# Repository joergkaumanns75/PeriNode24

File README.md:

# PeriCharger – Ladegerät für 6 × 12 V / 2,4 Ah Blei-Gel (Perinode24)

Sechs unabhängige Ladekanäle (IUoU: Konstantstrom 0,6 A → 14,4 V → Erhaltung 13,65 V, temperaturkompensiert),
gesteuert von einem ESP32-S3 mit Weboberfläche. Versorgung: 24 V DC oder 230/240 V AC über ein Netzteil (Mean Well LRS-100-24).

| Ordner | Inhalt |
|---|---|
| [`kicad/`](kicad/) | KiCad-Projekt (`perinode24.kicad_pro`): Schaltplan (7 Blätter), 4-lagige Leiterplatte, JLCPCB-Stückliste mit LCSC-Nummern, Generator-Werkzeuge – siehe [kicad/README.md](kicad/README.md) |
| [`firmware/`](firmware/) | PlatformIO-Projekt für den ESP32-S3 (Arduino-Core 3.x): Ladesteuerung, WLAN, Weboberfläche, Host-Simulation – siehe [firmware/README.md](firmware/README.md) |

**Stand Leiterplatte:** geroutet und DRC-sauber. Noch sind 6 kurze Signalverbindungen an den Spannungsreglern von Hand zu ziehen (Liste in kicad/README.md).
Die Firmware ist auf dem PC simuliert und getestet, aber noch nicht auf echter Hardware.

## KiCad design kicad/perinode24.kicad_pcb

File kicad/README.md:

# Perinode24 – KiCad-Projekt Ladegerät 6 × 12 V / 2,4 Ah

Öffnen: `perinode24.kicad_pro` (KiCad 7; KiCad 8/9 konvertiert beim Speichern).

| Datei | Inhalt |
|---|---|
| `perinode24.kicad_sch` | Hauptblatt (A2): 24-V-DC-Eingang und Netzteil-Eingang mit Ideal-Dioden-ODER (LM74700), 5 V (LMR16006), 3,3 V (TLV75733), ESP32-S3-WROOM-1-N8R8, USB-C, I²C/1-Wire/OLED |
| `kanal1…6.kicad_sch` | je ein Ladekanal (A3): TPS54160A, CC/CV-Sollwertsteuerung, INA226 + INA181, Verpolschutz, PTC, Akku- und Sensoranschluss |
| `perinode24.kicad_sym` | Projektsymbole: TPS54160A (MSOP-10 PowerPAD), N-MOSFET SO-8 |
| `bom_jlcpcb.csv` | Stückliste im JLCPCB-Format (Comment, Designator, Footprint, LCSC Part #) |
| `perinode24_schaltplan.pdf` | PDF-Export aller Blätter |
| `tools/gen_schematic.py` | Generator – Werte/LCSC-Nummern in der Tabelle `P` ändern und neu erzeugen |

Jedes Bauteil hat die Felder **LCSC** und **MPN**. Diese Felder werden von JLCPCB-Exporttools übernommen, zum Beispiel vom Plugin „Fabrication Toolkit“ oder von „kicad-jlcpcb-tools“.

## Vor der Bestellung prüfen

- **C106/C206/… 47 pF (C1671):** Diese LCSC-Nummer ist nicht verifiziert. Alle anderen Nummern wurden im LCSC/JLCPCB-Katalog nachgeschlagen. Lagerbestand und die Einstufung Basic/Extended ändern sich laufend.
- **Alles SMD:** Stecker sind JST PH SMD.
  - J1/J2 (24 V): S6B-PH-SM4-TB, je 3 Pins parallel für + und −, 2 A pro Pin.
  - Akku + DS18B20: S4B-PH-SM4-TB mit Belegung 1 = Akku +, 2 = Akku − / GND, 3 = DQ, 4 = 3,3 V.
  - Display: Qwiic-Buchse SM04B-SRSS-TB.
  - Nur die Gehäuselaschen der USB-C-Buchse gehen durchs Board.
- **Footprint Drossel:** Die FXL1360-680-M (13,45 × 12,6 mm) liegt auf dem KiCad-Footprint L_TaiTech_TMPC1265_13.5x12.5mm. Pads gegen das Datenblatt des Herstellers prüfen.
- **TPS54160A:** Geprüft gegen das TI-Datenblatt SLVSB56C (Rev. C, Feb. 2014). Pinbelegung, VREF 0,8 V, EN-Schwelle 1,11–1,36 V (EN max. 5 V), BOOT 0,1 µF und Softstart (10 nF → 4 ms) stimmen. RT = 206033/f^1,0888, mit 390 k ergeben sich 316 kHz. Kompensation nach Abschnitt 9.2.2.10 (gmEA 97 µA/V, gmPS 6 A/V): Bei 0,6 A und einer wirksamen Ausgangskapazität von ca. 8 µF ergeben sich Rc ≈ 13,7 k und Cc ≈ 14 nF. Die gewählten 18 k / 15 nF ergeben eine Durchtrittsfrequenz fc ≈ 10 kHz, zulässig sind 4,1…15,9 kHz. Trotzdem mit Lastsprung messen.
- **Drossel:** FXL1360-680-M (C526032), 68 µH, 3 A Nennstrom, 4,5 A laut JLCPCB-Listing. Damit hat sie genug Reserve über der TPS54160A-Strombegrenzung (typ. 2,7 A). Ob die 4,5 A der Sättigungsstrom sind, in der I(L)-Kurve des Datenblatts prüfen.
- **ERC:** In KiCad ausführen. Die Prüfung hier erfolgte über den Netzlisten-Export: keine offenen Netze außer den bewusst nicht beschalteten Pins.
- Die Verbindungen sind über **Netzlabels** an Pin-Stichleitungen realisiert. Elektrisch ist das vollständig. Für eine schönere Darstellung kann man die Bauteile in KiCad umsortieren.

## Leiterplatte (`perinode24.kicad_pcb`)

**Stand: geroutet. DRC ohne Abstands-, Rand-, Bohr- oder Breitenverletzungen. 6 kurze Signalverbindungen sind noch von Hand zu ziehen** (siehe unten).

- **Format:** 200 × 131 mm, 4 Lagen, 1,6 mm (JLCPCB JLC04161H-7628), alle Bauteile SMD und oben.
- **Lagenaufbau:**
  - F.Cu: Bauteile, Signale, GND-Fläche
  - In1: durchgehende GND-Fläche (keine Leiterbahnen)
  - In2: Signale und +24-V-Fläche
  - B.Cu: Signale, GND-Fläche
- **Stitching:** rund 610 Vias im 5-mm-Raster verbinden die GND-Flächen. Unter der ESP32-Antenne ist auf allen Lagen kein Kupfer.
- **Netzklassen:**
  - Power24 0,8 mm: +24 V, Eingänge
  - Power 0,5 mm: Schaltknoten, Ausgang, Akku
  - Sense 0,3 mm: Shunt
  - Supply 0,3 mm: GND, +5 V, +3,3 V
  - Default 0,25 mm
  - Abstand 0,2 mm, Randabstand 0,2 mm (JLCPCB: ≥ 0,2 mm bei gefrästen Kanten), Mindestbahnbreite 0,12 mm
- `docs/platine_F.png`, `platine_In2.png`, `platine_B.png`: Ansichten der Lagen. `docs/drc_bericht.txt`: DRC-Bericht.

### Noch von Hand zu verbinden (in KiCad mit „Leiterbahn verlegen“, X)
| Kanal | Netz | von | nach |
|---|---|---|---|
| 1 | SS | U101 Pin 4 | C104 Pin 1 |
| 4 | SS | U401 Pin 4 | C404 Pin 1 |
| 6 | SS | U601 Pin 4 | C604 Pin 1 |
| 2 | EN_N | U201 Pin 3 | vorhandene Bahn auf In2 |
| 3 | EN_N | U301 Pin 3 | vorhandene Bahn auf In2 |
| 5 | EN_N | U501 Pin 3 → R504 Pin 1 → vorhandene Bahn (1,8 mm) |

Die Pins 3/4 des TPS54160A liegen im 0,5-mm-Raster zwischen bereits verlegten Bahnen. Am einfachsten verschiebt man die Bahn an Pin 5 (RT) etwas oder führt die Verbindung mit einem Via über B.Cu, wo unter dem IC Platz ist. Zwei winzige GND-Flächeninseln auf F.Cu werden nach dem Nachrouten mit einem Via angebunden oder können gelöscht werden. Danach Zonen füllen (B) und die DRC erneut ausführen.

### Wie die Leiterplatte entstanden ist (Werkzeuge in `tools/`)
1. `gen_pcb.py`: Footprints aus der Netzliste, Platzierung (Ankerplätze und automatische Platzierung), Umriss, Bohrungen, Flächen
2. `preroute.py`: kritische Anschlüsse der fein gerasterten ICs vorverlegen (TPS VIN → +24-V-Via, GND-Pins → Via bzw. Thermal-Pad) und fixieren
3. Export DSN, `dsn_classes.py` (Netzklassen ergänzen, GND für Freerouting ausblenden), **Freerouting 2.5.0** mit 10 Durchgängen
4. `import_ses.py`: Session einspielen
5. `postroute.py`: +24-V-Fläche auf In2, offene Pads an Flächen, Lücken schließen, Inseln, Stitching-Vias (alles mit KiCads Kollisionsprüfung)
6. `maze.py`: A*-Router für einzelne Restverbindungen
7. `check_pcb.py`: Zonen füllen und DRC. `set_netclasses.py` nach jedem Speichern über die API ausführen, weil KiCad 7 headless die Projekt-Netzklassen zurücksetzt.

Nach dem Nachrouten in KiCad: Gerber, Bohrdaten, BOM und CPL für JLCPCB erzeugen, zum Beispiel mit dem Plugin „Fabrication Toolkit“, das das Feld LCSC übernimmt.

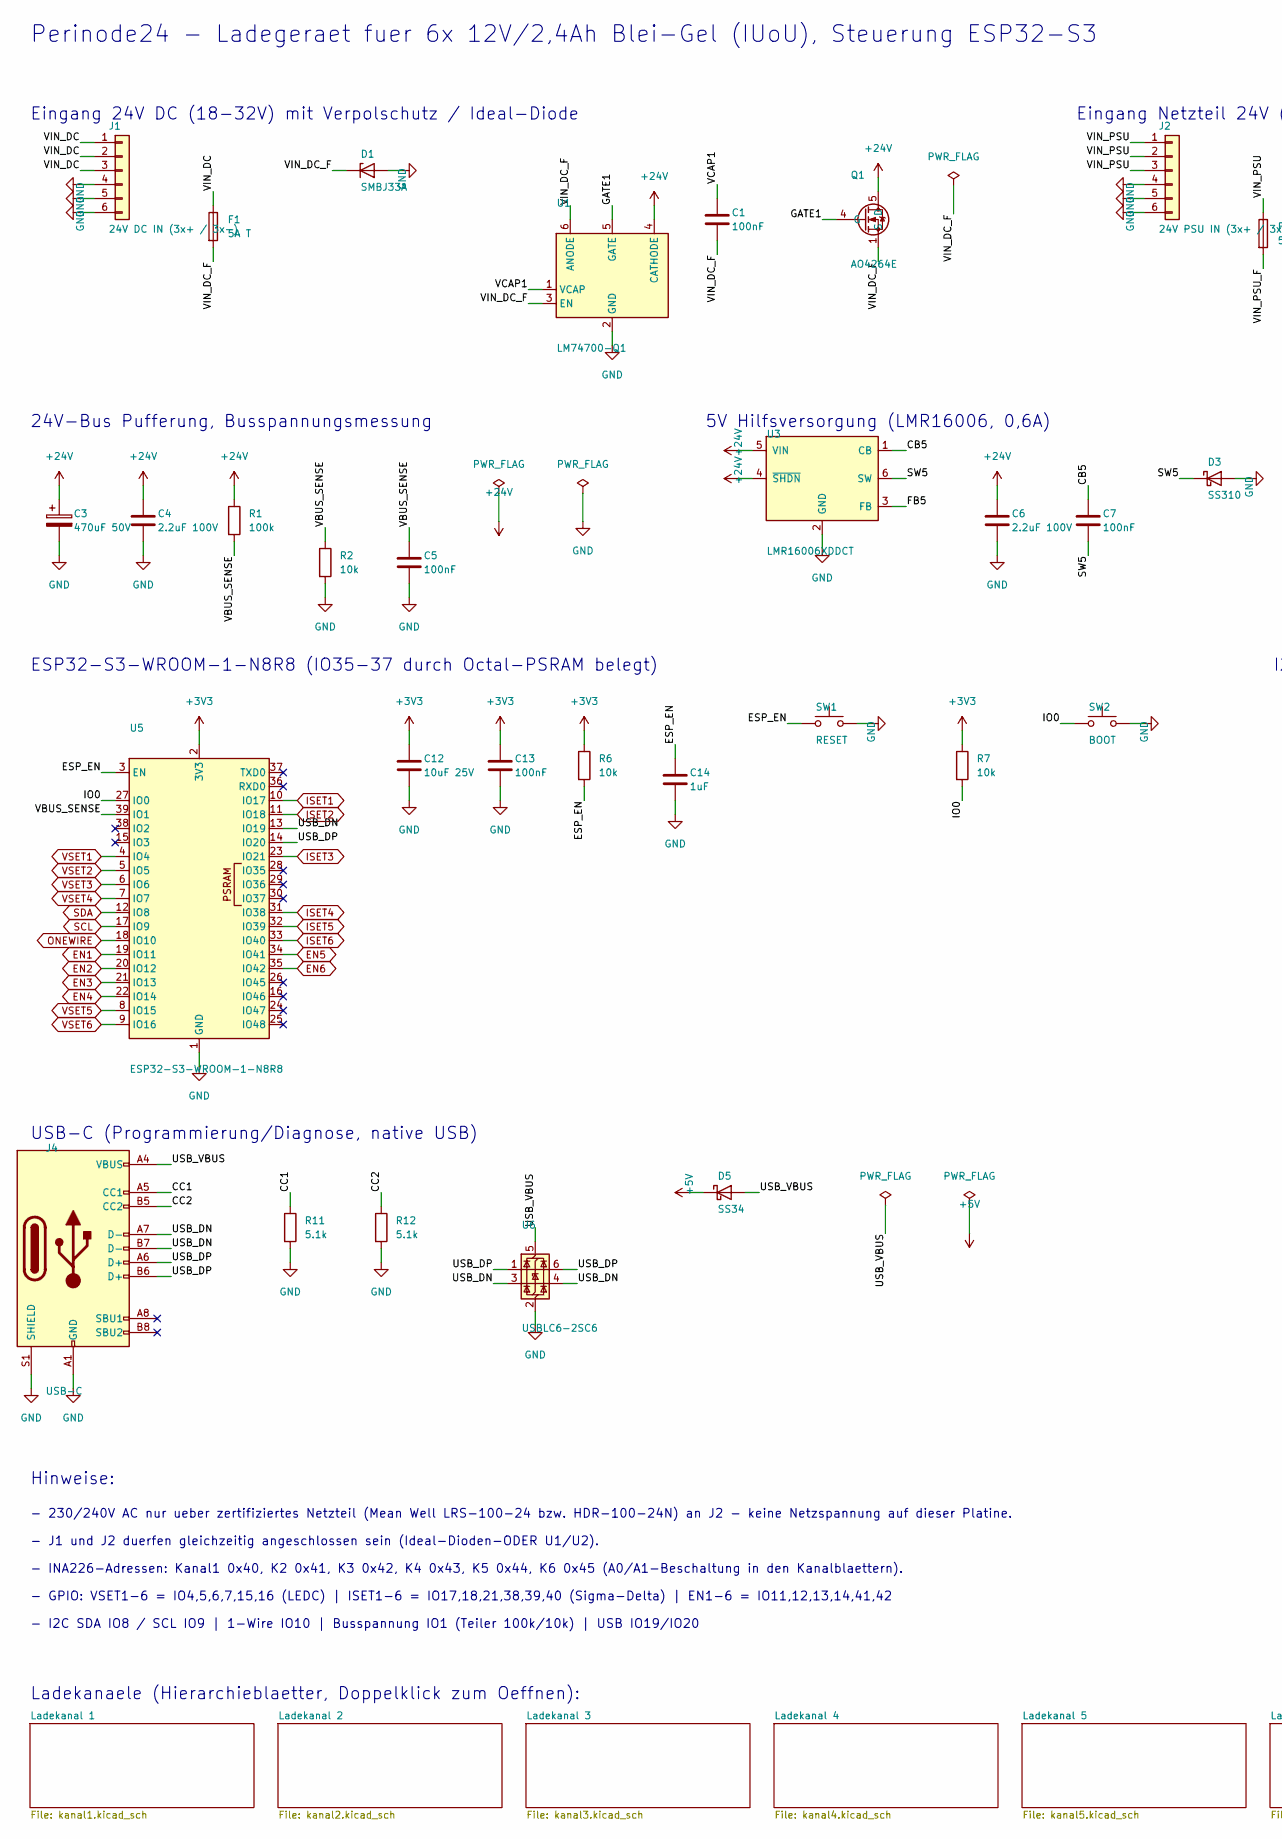
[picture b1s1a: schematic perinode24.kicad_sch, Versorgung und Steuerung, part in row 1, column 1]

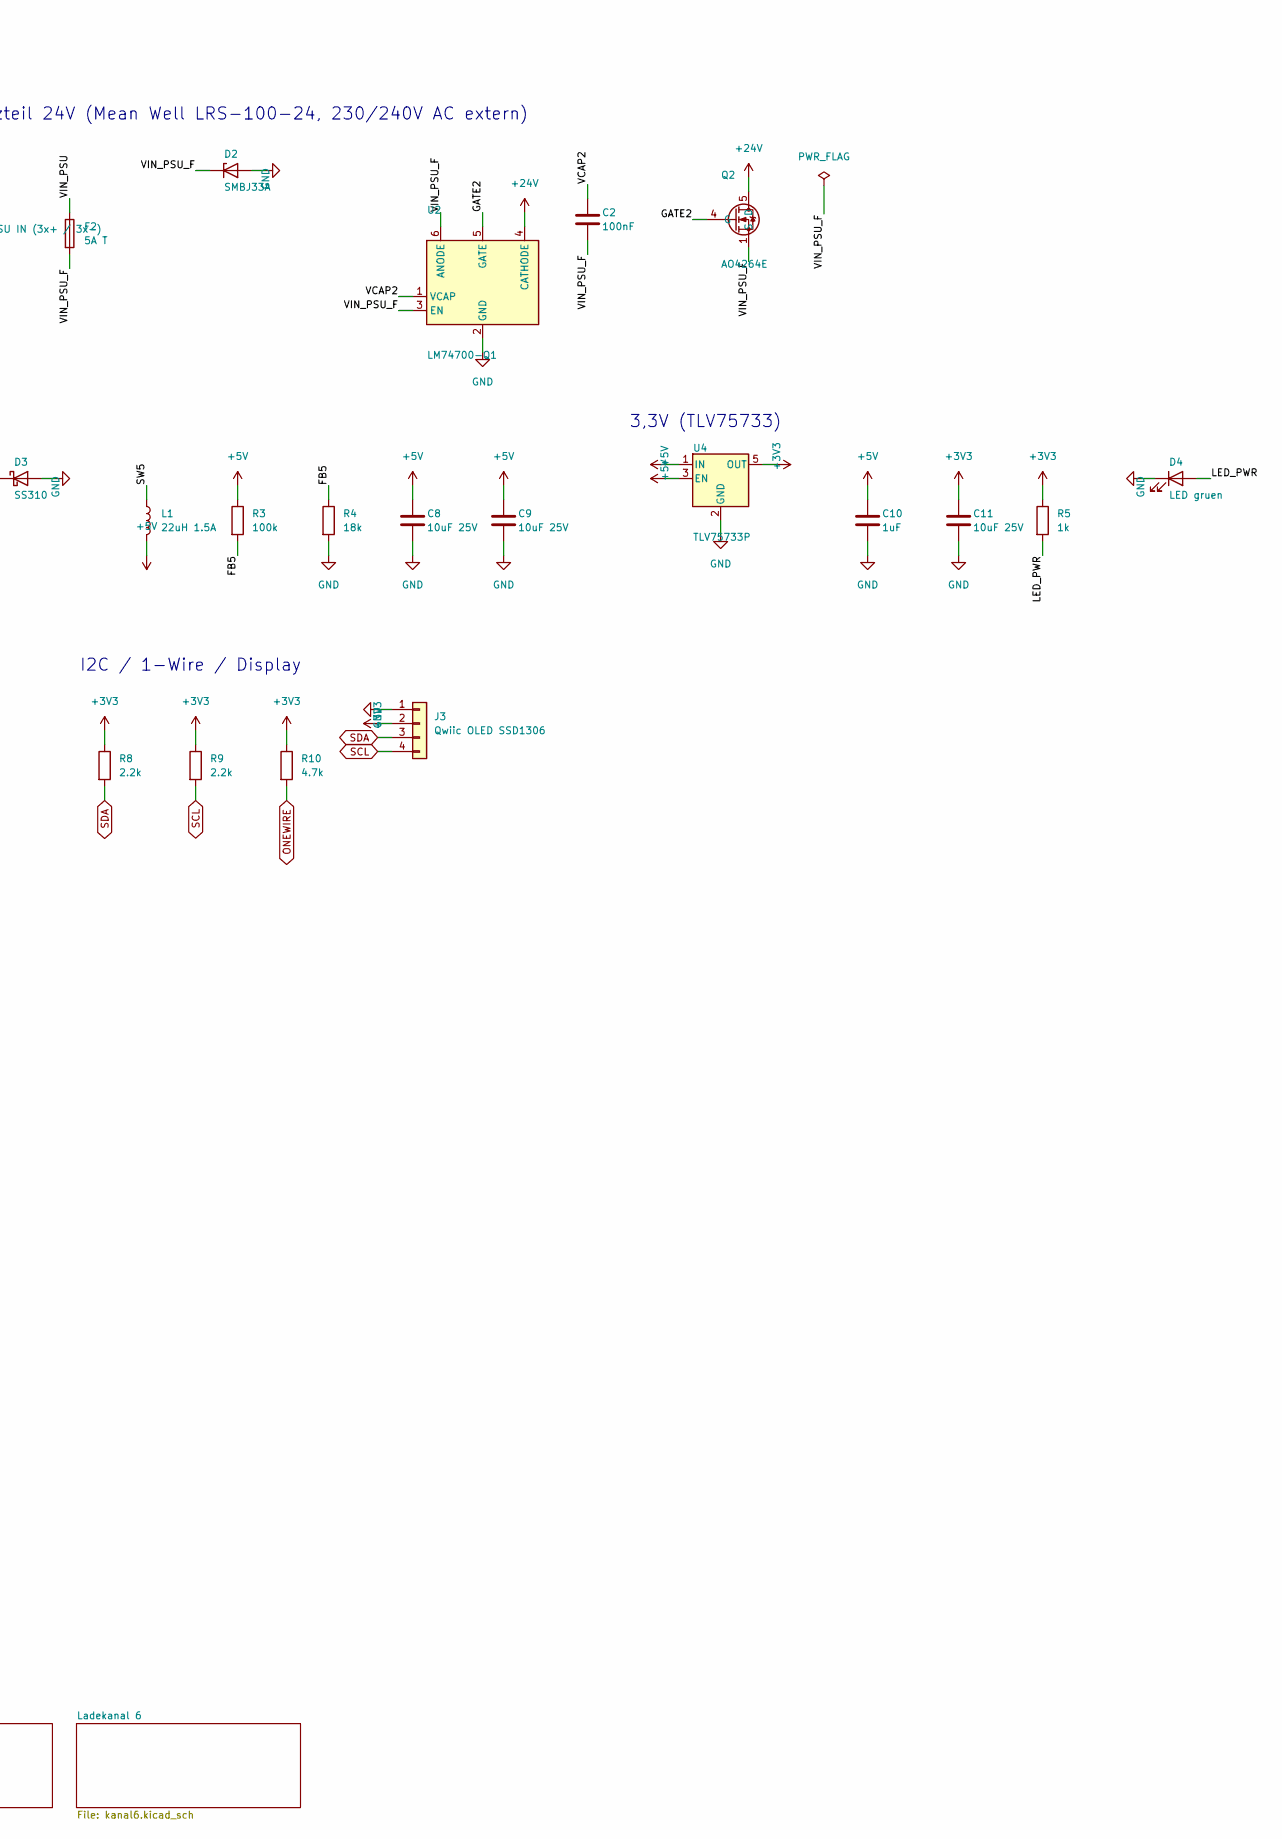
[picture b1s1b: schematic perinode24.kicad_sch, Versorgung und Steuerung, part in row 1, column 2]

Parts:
C1, C2, C5, C7, C13: 100nF; C_0603_1608Metric; MPN CC0603KRX7R9BB104; LCSC C14663
C3: 470uF 50V; CP_Elec_10x12.5; MPN EFVM050ADA471M10C0; LCSC C22469994
C4, C6: 2.2uF 100V; C_1210_3225Metric; MPN CL32B225KCJSNNE; LCSC C55151
C8, C9, C11, C12: 10uF 25V; C_0805_2012Metric; MPN CL21A106KAYNNNE; LCSC C15850
C10, C14: 1uF; C_0603_1608Metric; MPN CL10A105KB8NNNC; LCSC C15849
D1, D2: SMBJ33A; D_SMB; MPN SMBJ33A; LCSC C353366
D3: SS310; D_SMA; MPN SS310; LCSC C15874
D4: LED gruen; LED_0603_1608Metric; MPN 19-217/GHC-YR1S2/3T; LCSC C72043
D5: SS34; D_SMA; MPN SS34; LCSC C8678
F1, F2: 5A T; Fuse_Littelfuse-NANO2-451_453; MPN 0452005.MRL; LCSC C66503
J1: 24V DC IN (3x+ / 3x-); JST_PH_S6B-PH-SM4-TB_1x06-1MP_P2.00mm_Horizontal; MPN S6B-PH-SM4-TB(LF)(SN); LCSC C265405
J2: 24V PSU IN (3x+ / 3x-); JST_PH_S6B-PH-SM4-TB_1x06-1MP_P2.00mm_Horizontal; MPN S6B-PH-SM4-TB(LF)(SN); LCSC C265405
J3: Qwiic OLED SSD1306; JST_SH_SM04B-SRSS-TB_1x04-1MP_P1.00mm_Horizontal; MPN SM04B-SRSS-TB(LF)(SN); LCSC C160404
J4: USB-C; USB_C_Receptacle_HRO_TYPE-C-31-M-12; MPN TYPE-C-31-M-12; LCSC C165948
L1: 22uH 1.5A; L_Bourns_SRN6045TA; MPN SRN6045-220M; LCSC C780213
Q1, Q2: AO4264E; SOIC-8_3.9x4.9mm_P1.27mm; MPN AO4264E; LCSC C334232
R1, R3: 100k; R_0603_1608Metric; MPN 0603WAF1003T5E; LCSC C25803
R2, R6, R7: 10k; R_0603_1608Metric; MPN 0603WAF1002T5E; LCSC C25804
R4: 18k; R_0603_1608Metric; MPN 0603WAF1802T5E; LCSC C25810
R5: 1k; R_0603_1608Metric; MPN 0603WAF1001T5E; LCSC C21190
R8, R9: 2.2k; R_0603_1608Metric; MPN 0603WAF2201T5E; LCSC C4190
R10: 4.7k; R_0603_1608Metric; MPN 0603WAF4701T5E; LCSC C23162
R11, R12: 5.1k; R_0603_1608Metric; MPN 0603WAF5101T5E; LCSC C23186
SW1: RESET; SW_Push_1P1T_XKB_TS-1187A; MPN TS-1187A-B-A-B; LCSC C318884
SW2: BOOT; SW_Push_1P1T_XKB_TS-1187A; MPN TS-1187A-B-A-B; LCSC C318884
U1, U2: LM74700-Q1; SOT-23-6; MPN LM74700QDBVRQ1; LCSC C2941042
U3: LMR16006XDDCT; TSOT-23-6; MPN LMR16006XDDCT; LCSC C2070731
U4: TLV75733P; SOT-23-5; MPN TLV75733PDBVR; LCSC C485517
U5: ESP32-S3-WROOM-1-N8R8; ESP32-S3-WROOM-1; MPN ESP32-S3-WROOM-1-N8R8; LCSC C2913201
U6: USBLC6-2SC6; SOT-23-6; MPN USBLC6-2SC6; LCSC C7519

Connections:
+3V3: C11.1, C12.1, C13.1, J3.2, R5.1, R6.1, R7.1, R8.1, R9.1, R10.1, U4.5 (OUT), U5.2 (3V3); also elsewhere on the board
+5V: C8.1, C9.1, C10.1, D5.1 (K), L1.2, R3.1, U4.1 (IN), U4.3 (EN); also elsewhere on the board
+24V: C3.1, C4.1, C6.1, Q1.5 (D), Q1.6 (D), Q1.7 (D), Q1.8 (D), Q2.5 (D), Q2.6 (D), Q2.7 (D), Q2.8 (D), R1.1, U1.4 (CATHODE), U2.4 (CATHODE), U3.4 (~SHDN), U3.5 (VIN); also elsewhere on the board
/CB5: C7.1, U3.1 (CB)
/CC1: J4.A5 (CC1), R11.1
/CC2: J4.B5 (CC2), R12.1
/ESP_EN: C14.1, R6.2, SW1.1, U5.3 (EN)
/FB5: R3.2, R4.1, U3.3 (FB)
/GATE1: Q1.4 (G), U1.5 (GATE)
/GATE2: Q2.4 (G), U2.5 (GATE)
/IO0: R7.2, SW2.1, U5.27 (IO0)
/LED_PWR: D4.2 (A), R5.2
/SW5: C7.2, D3.1 (K), L1.1, U3.6 (SW)
/USB_DN: J4.A7 (D-), J4.B7 (D-), U5.13 (IO19), U6.3 (I/O2), U6.4 (I/O2)
/USB_DP: J4.A6 (D+), J4.B6 (D+), U5.14 (IO20), U6.1 (I/O1), U6.6 (I/O1)
/USB_VBUS: D5.2 (A), J4.A4 (VBUS), J4.A9 (VBUS), J4.B4 (VBUS), J4.B9 (VBUS), U6.5 (VBUS)
/VBUS_SENSE: C5.1, R1.2, R2.1, U5.39 (IO1)
/VCAP1: C1.1, U1.1 (VCAP)
/VCAP2: C2.1, U2.1 (VCAP)
/VIN_DC: F1.1, J1.1, J1.2, J1.3
/VIN_DC_F: C1.2, D1.1 (K), F1.2, Q1.1 (S), Q1.2 (S), Q1.3 (S), U1.3 (EN), U1.6 (ANODE)
/VIN_PSU: F2.1, J2.1, J2.2, J2.3
/VIN_PSU_F: C2.2, D2.1 (K), F2.2, Q2.1 (S), Q2.2 (S), Q2.3 (S), U2.3 (EN), U2.6 (ANODE)
EN1: U5.19 (IO11); also elsewhere on the board
EN2: U5.20 (IO12); also elsewhere on the board
EN3: U5.21 (IO13); also elsewhere on the board
EN4: U5.22 (IO14); also elsewhere on the board
EN5: U5.34 (IO41); also elsewhere on the board
EN6: U5.35 (IO42); also elsewhere on the board
GND: C3.2, C4.2, C5.2, C6.2, C8.2, C9.2, C10.2, C11.2, C12.2, C13.2, C14.2, D1.2 (A), D2.2 (A), D3.2 (A), D4.1 (K), J1.4, J1.5, J1.6, J2.4, J2.5, J2.6, J3.1, J4.A1 (GND), J4.A12 (GND), J4.B1 (GND), J4.B12 (GND), J4.S1 (SHIELD), R2.2, R4.2, R11.2, R12.2, SW1.2, SW2.2, U1.2 (GND), U2.2 (GND), U3.2 (GND), U4.2 (GND), U5.1 (GND), U5.40 (GND), U5.41 (GND), U6.2 (GND); also elsewhere on the board
ISET1: U5.10 (IO17); also elsewhere on the board
ISET2: U5.11 (IO18); also elsewhere on the board
ISET3: U5.23 (IO21); also elsewhere on the board
ISET4: U5.31 (IO38); also elsewhere on the board
ISET5: U5.32 (IO39); also elsewhere on the board
ISET6: U5.33 (IO40); also elsewhere on the board
ONEWIRE: R10.2, U5.18 (IO10); also elsewhere on the board
SCL: J3.4, R9.2, U5.17 (IO9); also elsewhere on the board
SDA: J3.3, R8.2, U5.12 (IO8); also elsewhere on the board
VSET1: U5.4 (IO4); also elsewhere on the board
VSET2: U5.5 (IO5); also elsewhere on the board
VSET3: U5.6 (IO6); also elsewhere on the board
VSET4: U5.7 (IO7); also elsewhere on the board
VSET5: U5.8 (IO15); also elsewhere on the board
VSET6: U5.9 (IO16); also elsewhere on the board

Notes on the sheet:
Hinweise:
Perinode24 - Ladegeraet fuer 6x 12V/2,4Ah Blei-Gel (IUoU), Steuerung ESP32-S3
I2C / 1-Wire / Display
3,3V (TLV75733)
5V Hilfsversorgung (LMR16006, 0,6A)
- J1 und J2 duerfen gleichzeitig angeschlossen sein (Ideal-Dioden-ODER U1/U2).
Eingang 24V DC (18-32V) mit Verpolschutz / Ideal-Diode
USB-C (Programmierung/Diagnose, native USB)
24V-Bus Pufferung, Busspannungsmessung
- GPIO: VSET1-6 = IO4,5,6,7,15,16 (LEDC) | ISET1-6 = IO17,18,21,38,39,40 (Sigma-Delta) | EN1-6 = IO11,12,13,14,41,42
- INA226-Adressen: Kanal1 0x40, K2 0x41, K3 0x42, K4 0x43, K5 0x44, K6 0x45 (A0/A1-Beschaltung in den Kanalblaettern).
Eingang Netzteil 24V (Mean Well LRS-100-24, 230/240V AC extern)
- I2C SDA IO8 / SCL IO9 | 1-Wire IO10 | Busspannung IO1 (Teiler 100k/10k) | USB IO19/IO20
- 230/240V AC nur ueber zertifiziertes Netzteil (Mean Well LRS-100-24 bzw. HDR-100-24N) an J2 - keine Netzspannung auf dieser Platine.
ESP32-S3-WROOM-1-N8R8 (IO35-37 durch Octal-PSRAM belegt)
Ladekanaele (Hierarchieblaetter, Doppelklick zum Oeffnen):

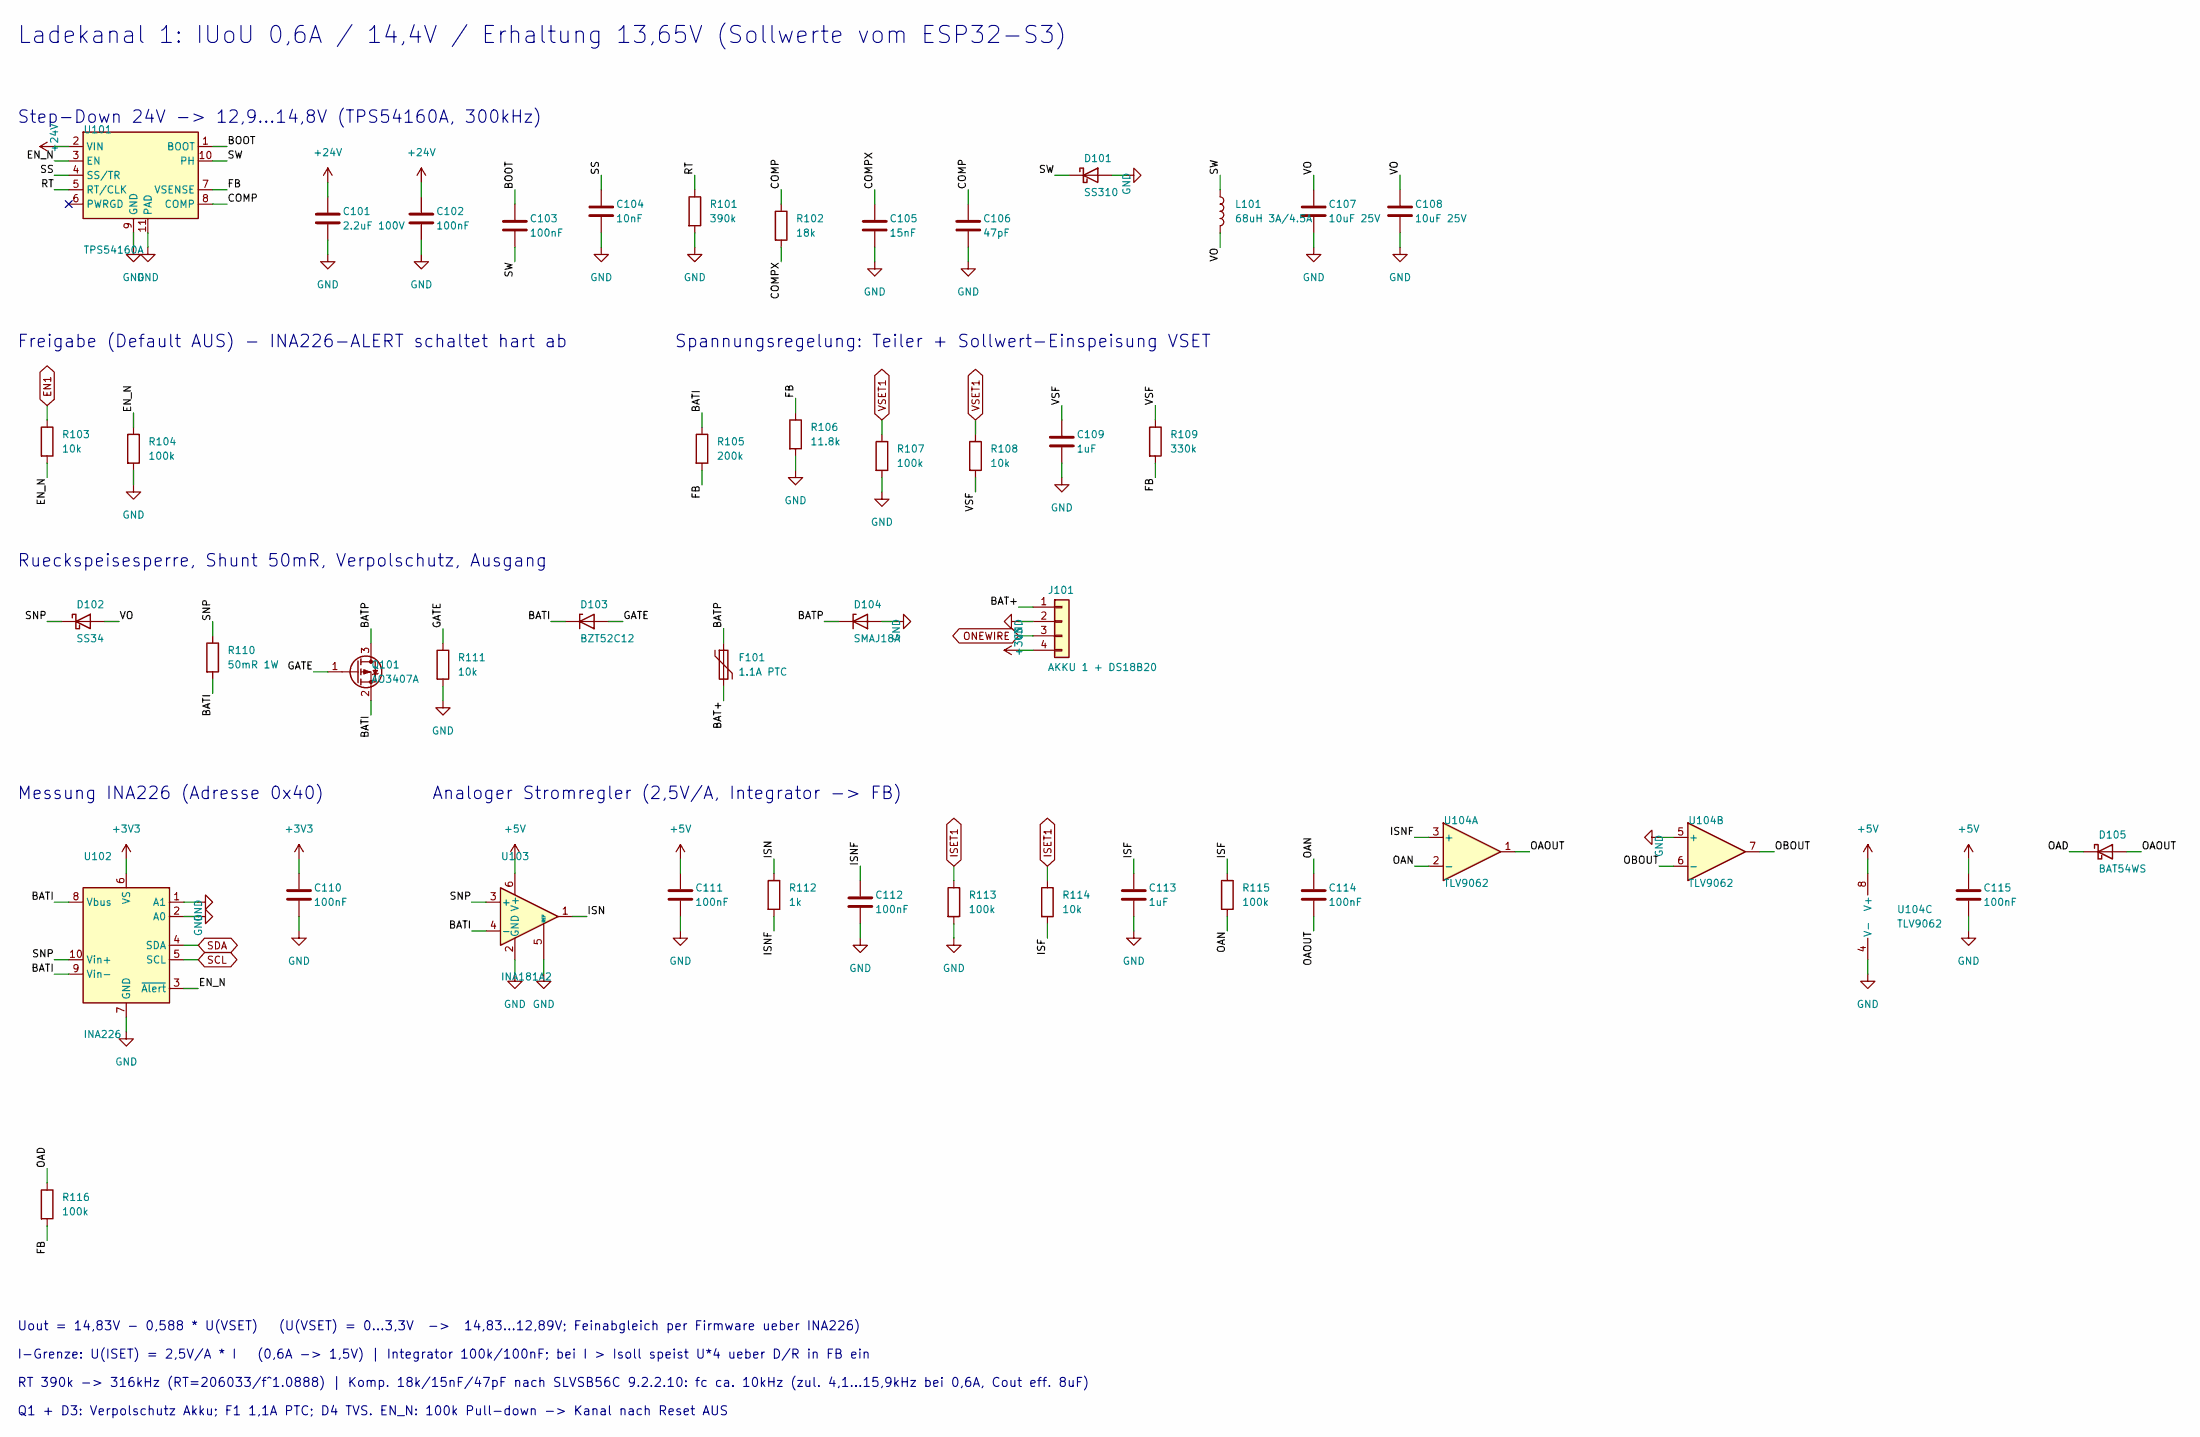
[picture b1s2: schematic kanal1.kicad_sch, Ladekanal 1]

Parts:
C101: 2.2uF 100V; C_1210_3225Metric; MPN CL32B225KCJSNNE; LCSC C55151
C102, C103, C110, C111, C112, C114, C115: 100nF; C_0603_1608Metric; MPN CC0603KRX7R9BB104; LCSC C14663
C104: 10nF; C_0603_1608Metric; MPN 0603B103K500NT; LCSC C57112
C105: 15nF; C_0603_1608Metric; MPN 0603B153K500CT; LCSC C296018
C106: 47pF; C_0603_1608Metric; MPN 0603CG470J500NT; LCSC C1671
C107, C108: 10uF 25V; C_0805_2012Metric; MPN CL21A106KAYNNNE; LCSC C15850
C109, C113: 1uF; C_0603_1608Metric; MPN CL10A105KB8NNNC; LCSC C15849
D101: SS310; D_SMA; MPN SS310; LCSC C15874
D102: SS34; D_SMA; MPN SS34; LCSC C8678
D103: BZT52C12; D_SOD-123; MPN BZT52C12; LCSC C2891780
D104: SMAJ18A; D_SMA; MPN SMAJ18A; LCSC C148219
D105: BAT54WS; D_SOD-323; MPN BAT54WS; LCSC C3040452
F101: 1.1A PTC; Fuse_1812_4532Metric; MPN 1812L110/16DR; LCSC C142746
J101: AKKU 1 + DS18B20; JST_PH_S4B-PH-SM4-TB_1x04-1MP_P2.00mm_Horizontal; MPN S4B-PH-SM4-TB(LF)(SN); LCSC C265102
L101: 68uH 3A/4.5A; L_TaiTech_TMPC1265_13.5x12.5mm; MPN FXL1360-680-M; LCSC C526032
Q101: AO3407A; SOT-23; MPN AO3407A; LCSC C15155
R101: 390k; R_0603_1608Metric; MPN 0603WAF3903T5E; LCSC C23150
R102: 18k; R_0603_1608Metric; MPN 0603WAF1802T5E; LCSC C25810
R103, R108, R111, R114: 10k; R_0603_1608Metric; MPN 0603WAF1002T5E; LCSC C25804
R104, R107, R113, R115, R116: 100k; R_0603_1608Metric; MPN 0603WAF1003T5E; LCSC C25803
R105: 200k; R_0603_1608Metric; MPN 0603WAF2003T5E; LCSC C25811
R106: 11.8k; R_0603_1608Metric; MPN RMC060311.8K1%N; LCSC C325665
R109: 330k; R_0603_1608Metric; MPN 0603WAF3303T5E; LCSC C23137
R110: 50mR 1W; R_1206_3216Metric; MPN RLM12FTCMR050; LCSC C912768
R112: 1k; R_0603_1608Metric; MPN 0603WAF1001T5E; LCSC C21190
U101: TPS54160A; MSOP-10-1EP_3x3mm_P0.5mm_EP1.68x1.88mm_ThermalVias; MPN TPS54160ADGQR; LCSC C390949
U102: INA226; VSSOP-10_3x3mm_P0.5mm; MPN INA226AIDGSR; LCSC C49851
U103: INA181A2; SOT-23-6; MPN INA181A2IDBVR; LCSC C2058784
U104: TLV9062; SOIC-8_3.9x4.9mm_P1.27mm; MPN TLV9062IDR; LCSC C398355

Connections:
+3V3: C110.1, J101.4, U102.6 (VS); also elsewhere on the board
+5V: C111.1, C115.1, U103.6 (V+), U104.8 (V+); also elsewhere on the board
+24V: C101.1, C102.1, U101.2 (VIN); also elsewhere on the board
/Ladekanal 1/BAT+: F101.2, J101.1
/Ladekanal 1/BATI: D103.1 (K), Q101.2 (S), R105.1, R110.2, U102.8 (Vbus), U102.9 (Vin-), U103.4 (-)
/Ladekanal 1/BATP: D104.1 (K), F101.1, Q101.3 (D)
/Ladekanal 1/BOOT: C103.1, U101.1 (BOOT)
/Ladekanal 1/COMP: C106.1, R102.1, U101.8 (COMP)
/Ladekanal 1/COMPX: C105.1, R102.2
/Ladekanal 1/EN_N: R103.2, R104.1, U101.3 (EN), U102.3 (~Alert)
/Ladekanal 1/FB: R105.2, R106.1, R109.2, R116.2, U101.7 (VSENSE)
/Ladekanal 1/GATE: D103.2 (A), Q101.1 (G), R111.1
/Ladekanal 1/ISF: C113.1, R114.2, R115.1
/Ladekanal 1/ISN: R112.1, U103.1
/Ladekanal 1/ISNF: C112.1, R112.2, U104.3 (+)
/Ladekanal 1/OAD: D105.1 (K), R116.1
/Ladekanal 1/OAN: C114.1, R115.2, U104.2 (-)
/Ladekanal 1/OAOUT: C114.2, D105.2 (A), U104.1
/Ladekanal 1/OBOUT: U104.6 (-), U104.7
/Ladekanal 1/RT: R101.1, U101.5 (RT/CLK)
/Ladekanal 1/SNP: D102.1 (K), R110.1, U102.10 (Vin+), U103.3 (+)
/Ladekanal 1/SS: C104.1, U101.4 (SS/TR)
/Ladekanal 1/SW: C103.2, D101.1 (K), L101.1, U101.10 (PH)
/Ladekanal 1/VO: C107.1, C108.1, D102.2 (A), L101.2
/Ladekanal 1/VSF: C109.1, R108.2, R109.1
EN1: R103.1; also elsewhere on the board
GND: C101.2, C102.2, C104.2, C105.2, C106.2, C107.2, C108.2, C109.2, C110.2, C111.2, C112.2, C113.2, C115.2, D101.2 (A), D104.2 (A), J101.2, R101.2, R104.2, R106.2, R107.2, R111.2, R113.2, U101.9 (GND), U101.11 (PAD), U102.1 (A1), U102.2 (A0), U102.7 (GND), U103.2 (GND), U103.5 (REF), U104.4 (V-), U104.5 (+); also elsewhere on the board
ISET1: R113.1, R114.1; also elsewhere on the board
ONEWIRE: J101.3; also elsewhere on the board
SCL: U102.5 (SCL); also elsewhere on the board
SDA: U102.4 (SDA); also elsewhere on the board
VSET1: R107.1, R108.1; also elsewhere on the board

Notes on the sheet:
Ladekanal 1: IUoU 0,6A / 14,4V / Erhaltung 13,65V (Sollwerte vom ESP32-S3)
Step-Down 24V -> 12,9...14,8V (TPS54160A, 300kHz)
Freigabe (Default AUS) - INA226-ALERT schaltet hart ab
Spannungsregelung: Teiler + Sollwert-Einspeisung VSET
Rueckspeisesperre, Shunt 50mR, Verpolschutz, Ausgang
Messung INA226 (Adresse 0x40)
Analoger Stromregler (2,5V/A, Integrator -> FB)
Uout = 14,83V - 0,588 * U(VSET) (U(VSET) = 0...3,3V -> 14,83...12,89V; Feinabgleich per Firmware ueber INA226)
I-Grenze: U(ISET) = 2,5V/A * I (0,6A -> 1,5V) | Integrator 100k/100nF; bei I > Isoll speist U*4 ueber D/R in FB ein
RT 390k -> 316kHz (RT=206033/f^1.0888) | Komp. 18k/15nF/47pF nach SLVSB56C 9.2.2.10: fc ca. 10kHz (zul. 4,1...15,9kHz bei 0,6A, Cout eff. 8uF)
Q1 + D3: Verpolschutz Akku; F1 1,1A PTC; D4 TVS. EN_N: 100k Pull-down -> Kanal nach Reset AUS

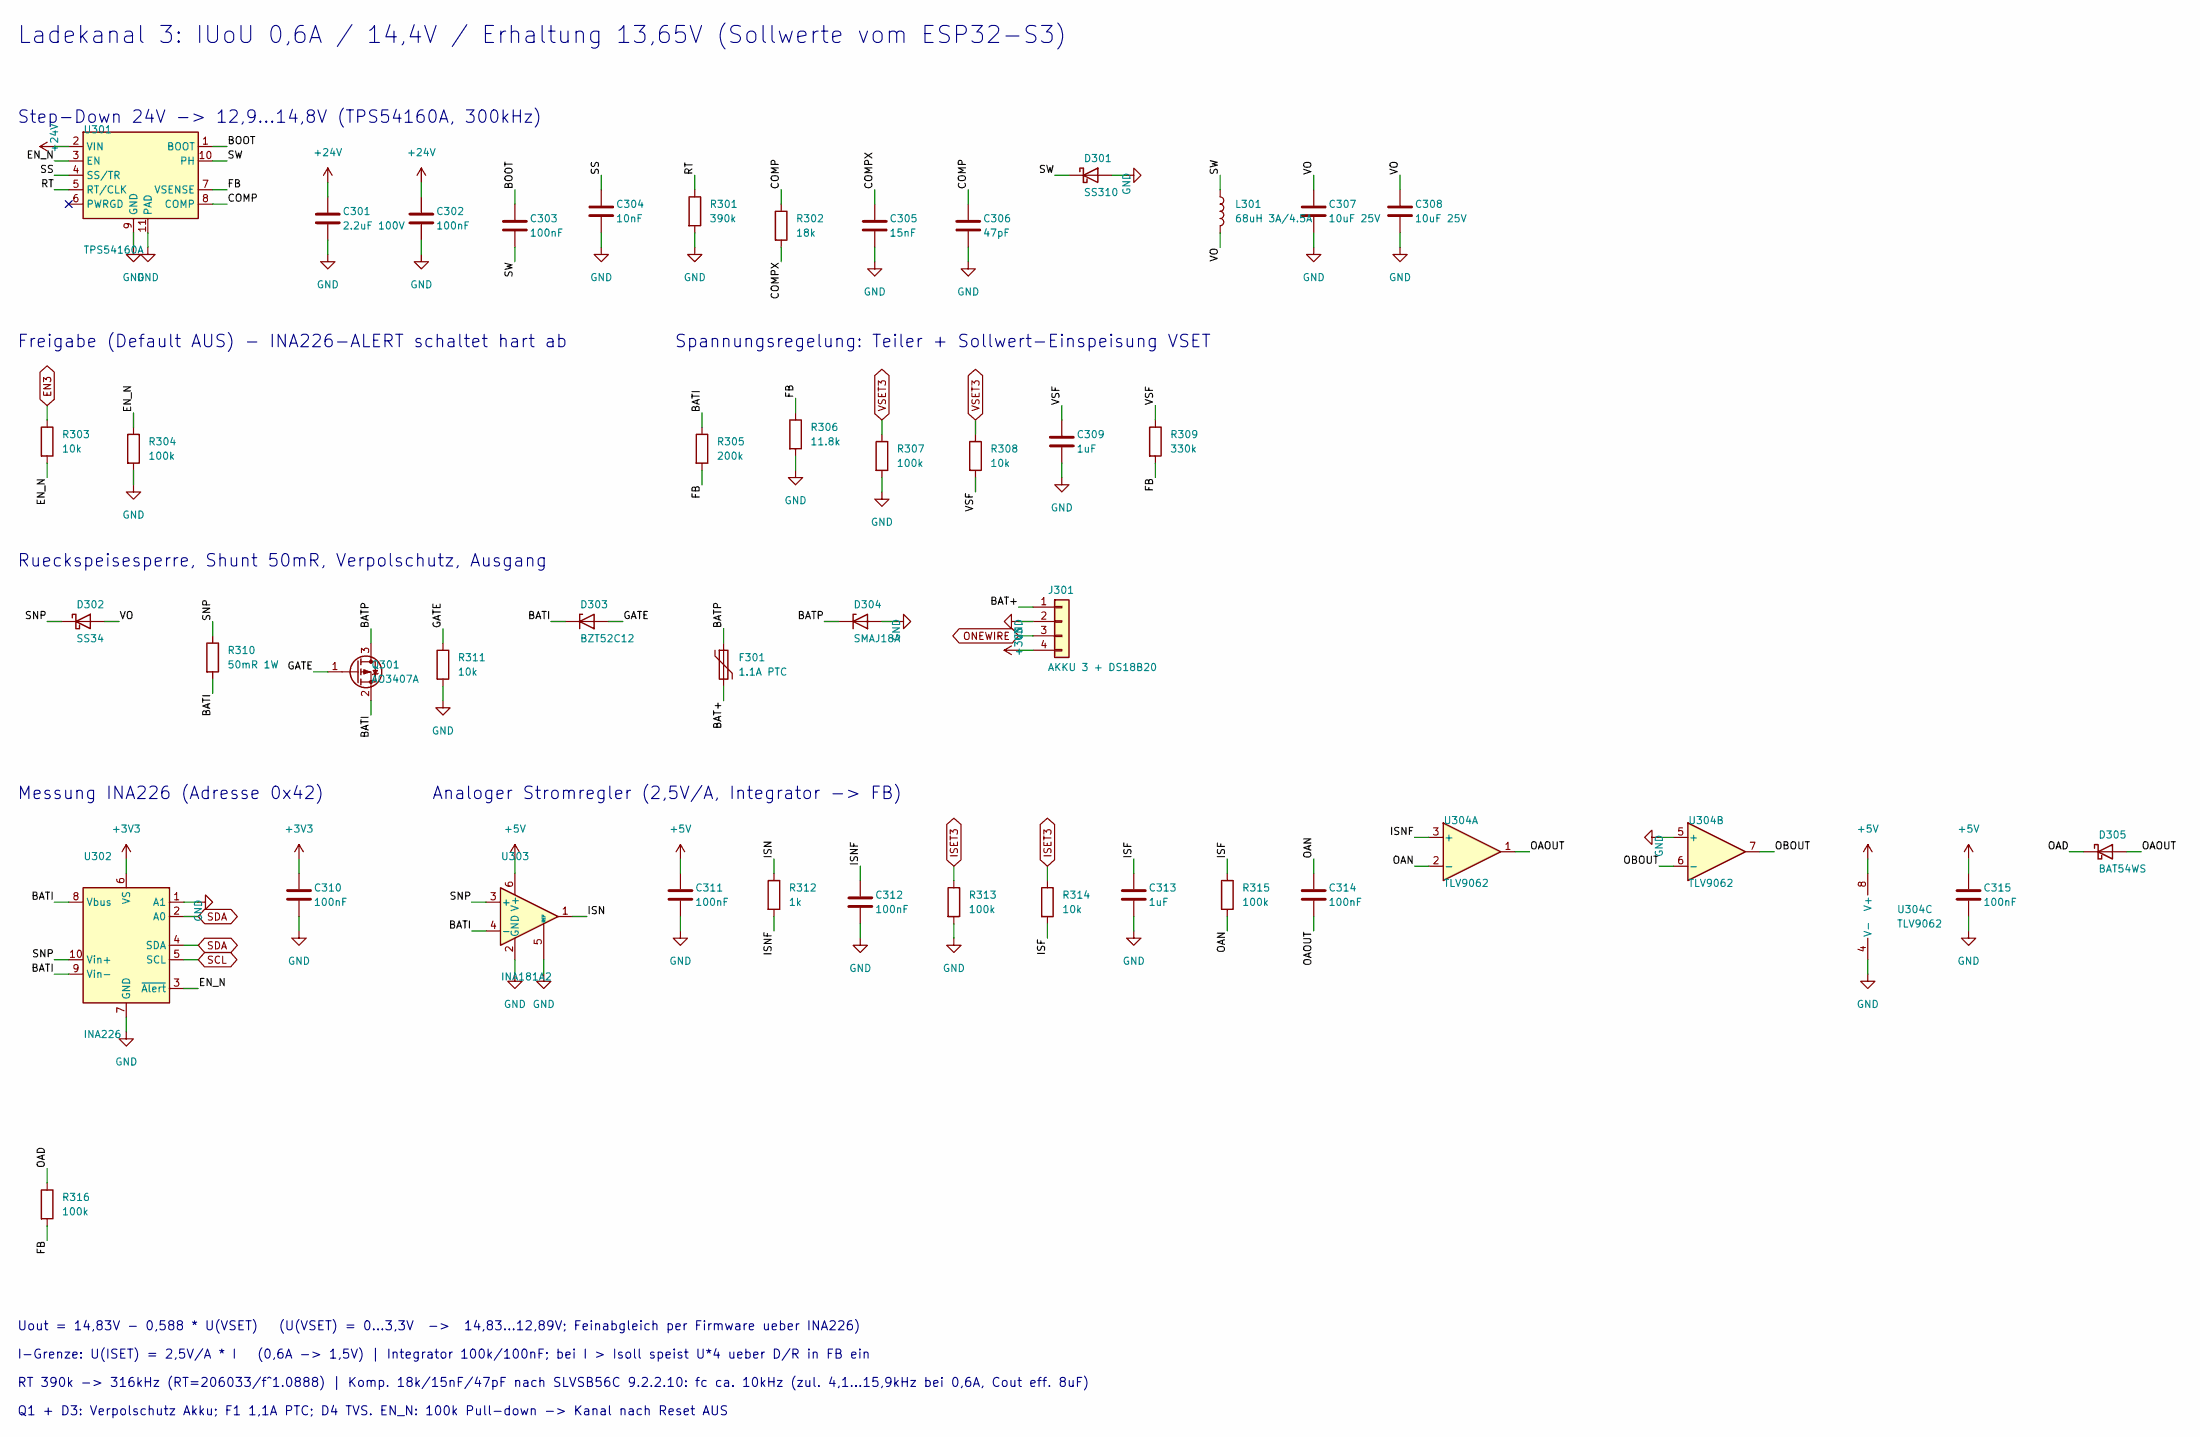
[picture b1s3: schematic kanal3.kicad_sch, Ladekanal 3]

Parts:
C301: 2.2uF 100V; C_1210_3225Metric; MPN CL32B225KCJSNNE; LCSC C55151
C302, C303, C310, C311, C312, C314, C315: 100nF; C_0603_1608Metric; MPN CC0603KRX7R9BB104; LCSC C14663
C304: 10nF; C_0603_1608Metric; MPN 0603B103K500NT; LCSC C57112
C305: 15nF; C_0603_1608Metric; MPN 0603B153K500CT; LCSC C296018
C306: 47pF; C_0603_1608Metric; MPN 0603CG470J500NT; LCSC C1671
C307, C308: 10uF 25V; C_0805_2012Metric; MPN CL21A106KAYNNNE; LCSC C15850
C309, C313: 1uF; C_0603_1608Metric; MPN CL10A105KB8NNNC; LCSC C15849
D301: SS310; D_SMA; MPN SS310; LCSC C15874
D302: SS34; D_SMA; MPN SS34; LCSC C8678
D303: BZT52C12; D_SOD-123; MPN BZT52C12; LCSC C2891780
D304: SMAJ18A; D_SMA; MPN SMAJ18A; LCSC C148219
D305: BAT54WS; D_SOD-323; MPN BAT54WS; LCSC C3040452
F301: 1.1A PTC; Fuse_1812_4532Metric; MPN 1812L110/16DR; LCSC C142746
J301: AKKU 3 + DS18B20; JST_PH_S4B-PH-SM4-TB_1x04-1MP_P2.00mm_Horizontal; MPN S4B-PH-SM4-TB(LF)(SN); LCSC C265102
L301: 68uH 3A/4.5A; L_TaiTech_TMPC1265_13.5x12.5mm; MPN FXL1360-680-M; LCSC C526032
Q301: AO3407A; SOT-23; MPN AO3407A; LCSC C15155
R301: 390k; R_0603_1608Metric; MPN 0603WAF3903T5E; LCSC C23150
R302: 18k; R_0603_1608Metric; MPN 0603WAF1802T5E; LCSC C25810
R303, R308, R311, R314: 10k; R_0603_1608Metric; MPN 0603WAF1002T5E; LCSC C25804
R304, R307, R313, R315, R316: 100k; R_0603_1608Metric; MPN 0603WAF1003T5E; LCSC C25803
R305: 200k; R_0603_1608Metric; MPN 0603WAF2003T5E; LCSC C25811
R306: 11.8k; R_0603_1608Metric; MPN RMC060311.8K1%N; LCSC C325665
R309: 330k; R_0603_1608Metric; MPN 0603WAF3303T5E; LCSC C23137
R310: 50mR 1W; R_1206_3216Metric; MPN RLM12FTCMR050; LCSC C912768
R312: 1k; R_0603_1608Metric; MPN 0603WAF1001T5E; LCSC C21190
U301: TPS54160A; MSOP-10-1EP_3x3mm_P0.5mm_EP1.68x1.88mm_ThermalVias; MPN TPS54160ADGQR; LCSC C390949
U302: INA226; VSSOP-10_3x3mm_P0.5mm; MPN INA226AIDGSR; LCSC C49851
U303: INA181A2; SOT-23-6; MPN INA181A2IDBVR; LCSC C2058784
U304: TLV9062; SOIC-8_3.9x4.9mm_P1.27mm; MPN TLV9062IDR; LCSC C398355

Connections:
+3V3: C310.1, J301.4, U302.6 (VS); also elsewhere on the board
+5V: C311.1, C315.1, U303.6 (V+), U304.8 (V+); also elsewhere on the board
+24V: C301.1, C302.1, U301.2 (VIN); also elsewhere on the board
/Ladekanal 3/BAT+: F301.2, J301.1
/Ladekanal 3/BATI: D303.1 (K), Q301.2 (S), R305.1, R310.2, U302.8 (Vbus), U302.9 (Vin-), U303.4 (-)
/Ladekanal 3/BATP: D304.1 (K), F301.1, Q301.3 (D)
/Ladekanal 3/BOOT: C303.1, U301.1 (BOOT)
/Ladekanal 3/COMP: C306.1, R302.1, U301.8 (COMP)
/Ladekanal 3/COMPX: C305.1, R302.2
/Ladekanal 3/EN_N: R303.2, R304.1, U301.3 (EN), U302.3 (~Alert)
/Ladekanal 3/FB: R305.2, R306.1, R309.2, R316.2, U301.7 (VSENSE)
/Ladekanal 3/GATE: D303.2 (A), Q301.1 (G), R311.1
/Ladekanal 3/ISF: C313.1, R314.2, R315.1
/Ladekanal 3/ISN: R312.1, U303.1
/Ladekanal 3/ISNF: C312.1, R312.2, U304.3 (+)
/Ladekanal 3/OAD: D305.1 (K), R316.1
/Ladekanal 3/OAN: C314.1, R315.2, U304.2 (-)
/Ladekanal 3/OAOUT: C314.2, D305.2 (A), U304.1
/Ladekanal 3/OBOUT: U304.6 (-), U304.7
/Ladekanal 3/RT: R301.1, U301.5 (RT/CLK)
/Ladekanal 3/SNP: D302.1 (K), R310.1, U302.10 (Vin+), U303.3 (+)
/Ladekanal 3/SS: C304.1, U301.4 (SS/TR)
/Ladekanal 3/SW: C303.2, D301.1 (K), L301.1, U301.10 (PH)
/Ladekanal 3/VO: C307.1, C308.1, D302.2 (A), L301.2
/Ladekanal 3/VSF: C309.1, R308.2, R309.1
EN3: R303.1; also elsewhere on the board
GND: C301.2, C302.2, C304.2, C305.2, C306.2, C307.2, C308.2, C309.2, C310.2, C311.2, C312.2, C313.2, C315.2, D301.2 (A), D304.2 (A), J301.2, R301.2, R304.2, R306.2, R307.2, R311.2, R313.2, U301.9 (GND), U301.11 (PAD), U302.1 (A1), U302.7 (GND), U303.2 (GND), U303.5 (REF), U304.4 (V-), U304.5 (+); also elsewhere on the board
ISET3: R313.1, R314.1; also elsewhere on the board
ONEWIRE: J301.3; also elsewhere on the board
SCL: U302.5 (SCL); also elsewhere on the board
SDA: U302.2 (A0), U302.4 (SDA); also elsewhere on the board
VSET3: R307.1, R308.1; also elsewhere on the board

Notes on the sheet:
Q1 + D3: Verpolschutz Akku; F1 1,1A PTC; D4 TVS. EN_N: 100k Pull-down -> Kanal nach Reset AUS
I-Grenze: U(ISET) = 2,5V/A * I (0,6A -> 1,5V) | Integrator 100k/100nF; bei I > Isoll speist U*4 ueber D/R in FB ein
Uout = 14,83V - 0,588 * U(VSET) (U(VSET) = 0...3,3V -> 14,83...12,89V; Feinabgleich per Firmware ueber INA226)
Spannungsregelung: Teiler + Sollwert-Einspeisung VSET
Step-Down 24V -> 12,9...14,8V (TPS54160A, 300kHz)
RT 390k -> 316kHz (RT=206033/f^1.0888) | Komp. 18k/15nF/47pF nach SLVSB56C 9.2.2.10: fc ca. 10kHz (zul. 4,1...15,9kHz bei 0,6A, Cout eff. 8uF)
Analoger Stromregler (2,5V/A, Integrator -> FB)
Messung INA226 (Adresse 0x42)
Ladekanal 3: IUoU 0,6A / 14,4V / Erhaltung 13,65V (Sollwerte vom ESP32-S3)
Freigabe (Default AUS) - INA226-ALERT schaltet hart ab
Rueckspeisesperre, Shunt 50mR, Verpolschutz, Ausgang
